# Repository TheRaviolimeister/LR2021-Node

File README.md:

# LR2021 Node

**A self-built LoRa mesh node with two Semtech LR2021 radios** (868 MHz + 433 MHz, both also 2.4 GHz).
It speaks **Meshtastic**, listens to **MeshCore** and has its own amateur-radio protocol for
text, images and files. Controlled by an app for Android, iOS, Windows and Linux – over Wi-Fi, Bluetooth,
USB or a serial cable.

## Hardware

| Part | Role |
|---|---|
| Orange Pi Zero 2W | the brain: runs the node service, Wi-Fi hotspot, Bluetooth, web UI |
| 2× ESP32-S3 DevKitC-1 | radio modems, one per LR2021 |
| Waveshare Core2021-HF / -LF (LR2021) | 850–930 MHz and 410–510 MHz, plus 2.4 GHz |
| GPS L76X | position |
| CP2102 | serial console / cable connection to the PC app |

Full part list: [docs/hardware/parts-list.md](docs/hardware/parts-list.md) ·
assembly and wiring: [docs/hardware/assembly.md](docs/hardware/assembly.md) ·
carrier PCB (ready to order): [hardware/carrier](hardware/carrier/README.md)

## Software

| Folder | Content | Docs |
|---|---|---|
| `firmware/` | ESP32 modem firmware (Arduino, RadioLib) | [docs/firmware.md](docs/firmware.md) |
| `Node/` | SD card image for the Orange Pi (Armbian), node service `lr2021d` | [docs/node.md](docs/node.md) |
| `App/source/` | Flutter app (Android, iOS, Windows, Linux) | [docs/app.md](docs/app.md) |
| `host/`, `modem_tool.py` | Python tools for testing modems on a PC | [docs/firmware.md](docs/firmware.md) |
| `docs/modem-protocol.md` | serial protocol between node and modems | – |

## Download

Ready-to-use builds are in the [releases](../../releases/latest): app for Android, iOS, Windows and Linux,
both modem firmwares and the node update package. The app updates itself from there.

## Building a node

1. Get the parts ([part list](docs/hardware/parts-list.md)) and wire them ([assembly](docs/hardware/assembly.md)).
2. Flash `LR2021-Modem-A.bin` to ESP32 A and `LR2021-Modem-B.bin` to ESP32 B ([firmware](docs/firmware.md)).
3. Build and write the SD card image ([node](docs/node.md)).
4. Install the app, connect to the node's Wi-Fi `LR2021-xxxx` and pick “Network (Pi)” ([app](docs/app.md)).

Transmitting on 70 cm with full power and the own LR protocol requires an amateur radio licence.
The app enforces the legal power limits for the license-free bands.

## Documentation

- Part list: [docs/hardware/parts-list.md](docs/hardware/parts-list.md)
- Assembly and wiring: [docs/hardware/assembly.md](docs/hardware/assembly.md)
- Carrier PCB (KiCad, Gerber, BOM): [hardware/carrier](hardware/carrier/README.md)
- ESP32 firmware: [docs/firmware.md](docs/firmware.md)
- Node software (SD card): [docs/node.md](docs/node.md)
- App: [docs/app.md](docs/app.md)
- Modem protocol: [docs/modem-protocol.md](docs/modem-protocol.md)
- Transmit power and licence: [docs/tx-power.md](docs/tx-power.md)

## License

- Software and firmware: **GPL-3.0** ([LICENSE](LICENSE))
- Hardware documentation (wiring, part list, plans): **CERN-OHL-S-2.0** ([LICENSE-HARDWARE](LICENSE-HARDWARE))
- **Attribution required:** see [NOTICE](NOTICE).

© 2026 Raviolimeister (RAV1805)

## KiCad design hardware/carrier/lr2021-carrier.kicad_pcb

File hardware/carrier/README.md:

# LR2021 Node – carrier board

A 172 × 106 mm two-layer PCB that replaces the perfboard and the point-to-point wiring. All modules
stay pluggable: the Orange Pi Zero 2W, both ESP32-S3 DevKitC-1 and both Core2021 modules sit in
female headers with generous space between them. The four antenna connectors are soldered to the
board, and the small SMD parts can be assembled by the PCB manufacturer. The 868 MHz path has a
1 W front end (power amplifier, low-noise amplifier with bypass) and a socket for a plug-in filter.

> Revision 1.3 has not been manufactured yet. Before ordering, print `fabrication/layout.svg` at
> 100 % and check the header positions against your own modules.

## Layout

```
 top edge:                 [868 LoRa]  [2.4G HF]  I2C I2C  [2.4G LF]  [433 LoRa]   I2C I2C I2C
             USB-C / J1  868 PA/LNA  Core2021-HF               Core2021-LF
             power input  filter      (both modules at the same height, mirrored)
                                    I2C  I2C  I2C  I2C  I2C
             ESP32 A            I2C header                                     ESP32 B
             (USB at the        I2C header  CONSOLE  GPS                       (USB at the
              bottom edge)  USB  Orange Pi Zero 2W (ports at the bottom edge)   bottom edge)
                         console
```

The layout is mirror-symmetric about the vertical centre line: both radio modules sit at the same
height, both ESP32 at the same distance from the side edges. The connectors for the console
adapter, GPS and I²C sit in the middle, directly above the Orange Pi pins they belong to. The USB
console (USB-C, CH340C, TX/RX LEDs) sits between ESP32 A and the Orange Pi at the bottom edge.
Signals run on the top layer; the bottom layer is a ground plane that is only interrupted by short
crossings (mainly where the I²C bus branches to the sockets). The bus between each ESP32 and its
radio module is routed without crossings: the lines of ESP32 A run in parallel along the left
edge and over the top end of its socket, the 5 V rail runs along the left edge and under the USB end
of ESP32 A and continues under the Orange Pi. The USB-C receptacle, the ESD protection and the
USB data lines have a fixed fan-out (0.5 mm pin pitch).

## Features

- **Four SMA antenna connectors (90°, through hole) on the top edge:** 868 MHz LoRa on the left,
  433 MHz LoRa on the right, the two 2.4 GHz connectors in the middle.
  - **RF lines:** each module pin is connected to its connector by a 50 Ω line (grounded
    coplanar waveguide: 1.55 mm track, 0.3 mm gap, solid ground underneath, ground via fence on
    both sides; calculated for the standard 1.6 mm FR4 two-layer stack). No other signal crosses
    or runs underneath an RF line. Lengths: 433 MHz and 2.4 GHz (LF module) about 17 mm,
    2.4 GHz (HF module) 36 mm, 868 MHz 19 mm module → filter socket, 9 mm filter socket → front end,
    10 mm front end → connector. A matched line of this length does not radiate; the loss is below
    0.05 dB (433 MHz), about 0.15 dB (868 MHz, all pieces) and about 0.3 dB (2.4 GHz, HF module).
  - **π network at every connector:** series 0 Ω resistor (fitted), a free 0603 shunt place on the
    module side (for a later low-pass or matching network, see "RF filters" below; on the 868 MHz
    line this place is the fitted 2.7 pF capacitor of the front end's antenna low-pass) and a shunt
    inductor to ground right at the connector.
  - **ESD protection:** the shunt inductor (L10 868 MHz: 68 nH, L11/L12 2.4 GHz: 15 nH, L13 433 MHz:
    100 nH, Murata LQG18HN) drains static charge from the antenna and its cable to ground. Its
    self-resonance lies just above the band (≥ 1.0 GHz, ≥ 2.8 GHz, ≥ 0.8 GHz), so in the band it is
    several hundred ohms: worst case 0.02–0.05 dB, in practice not measurable. The antenna ports of
    the radio modules and of the front end carry no DC (antennas may be DC shorts), so the DC path is
    harmless. This matters most for the front end (SE2435L: 1 kV HBM).
- **868 MHz front end (U8, Skyworks SE2435L):** see the section below – up to +30 dBm (1 W) at the
  connector, a low-noise amplifier with bypass that the firmware switches by the measured noise
  floor, and the plug-in filter socket J22.
- **Ten Qwiic / STEMMA QT sockets plus two 4-pin headers for I²C peripherals** (display, buttons,
  switches, sensors, I/O expanders). All of them are on the same bus: Orange Pi pins 3 (SDA) and
  5 (SCL), 4.7 kΩ pull-ups to 3.3 V. **3.3 V only:** do not connect modules that pull SDA/SCL up
  to 5 V.
- **One protected 5 V input:** USB-C (power only) or JST-XH J1 for the 18650 battery shield, with
  reverse-polarity protection (2 × P-MOSFET), 3 A resettable fuse, TVS diode and a power LED.
- **No back-feeding:** each ESP32 gets its 5 V through a Schottky diode, so a PC on the ESP32's USB
  port cannot feed the node's 5 V rail. All UART lines between the modules and to the console
  have 1 kΩ series resistors, so nothing is powered through the data lines when only one side
  is switched on. The console connector has no supply pin.
- **ESP32 reset and boot from the Orange Pi:** the Pi can pull EN and GPIO0 of each ESP32 low via
  a MOSFET (Pi pins 29/31 = EN/GPIO0 of ESP32 A, pins 32/33 = EN/GPIO0 of ESP32 B; high = pulled
  low). 10 kΩ pull-down resistors keep the MOSFETs off (ESP32 running) while the Pi boots or the
  Pi pins are not configured.
- **LR2021 DIO7 and DIO8** are connected to GPIO8 and GPIO9 of both ESP32 (not used by the
  current firmware, reserved).
- **USB console on the board:** USB-C J21 ("USB CONSOLE") with a CH340C USB serial converter and
  USBLC6-2SC6 ESD protection. It is the Orange Pi's debug console (UART0, 115200 Bd) and the
  "Node cable" connection of the app – one USB-C cable from the PC is enough. Two LEDs show the
  traffic: **TX** (red) = PC to node, **RX** (green) = node to PC.
  - The CH340C runs from the node's 3.3 V, the 5 V of the PC is not used at all (WCH self-powered
    mode). No current can flow between PC and node through the data lines, and the PC cannot feed
    the node. The COM port therefore only appears while the node is switched on.
  - Windows 10/11 installs the CH340 driver automatically (otherwise: WCH "CH341SER"); Linux and
    Android (USB-OTG) support it out of the box. The app recognises it as the node console.
- **Console adapter connector:** J3 (GND, RXD, TXD) for an external USB serial adapter such as the
  CP2102 module, in parallel to the on-board converter. Use only one of them at a time. Connect only
  GND, RXD and TXD of the adapter, not its 3.3 V / 5 V pin.
- Decoupling capacitors at both radio modules, an extra 22 µF at the Orange Pi's 5 V pins, GPS
  connector with PPS, ground planes on both layers.
- **Mounting holes:** M3 in the two top corners and two under the USB ends of the ESP32 sockets
  (mount the board before plugging in the ESP32). Orange Pi pin 6 (GND) is not connected on the
  carrier – it is connected to the other GND pins inside the Pi.

## 868 MHz front end

```
 Core2021-HF ── J22 filter socket ── SE2435L TR ─┬─ LNA (16 dB) / bypass ──┐
  (LORA_ANT)     (plug-in SAW)                   └─ PA (26 dB, up to 1 W) ─┴─ ANT1 ── low-pass ── SMA 868
```

- **U8 Skyworks SE2435L** (860–930 MHz front-end module): power amplifier up to +30 dBm, low-noise
  amplifier (16 dB gain, 2 dB noise figure) with bypass, transmit/receive switch. The output match
  (L2, C30, C31, L1), the harmonic traps (L7/C32 at the PA output, L9/C33 at the antenna side), the
  antenna low-pass (L8, L6, C9) and the supply decoupling follow the Skyworks SE2435L-EK5 evaluation
  board (+30 dBm, 868–930 MHz, ETSI/FCC). The values are a starting point: on a two-layer board the
  output match may need a small correction for the very last dB – check with a power meter.
- **Supply:** U9 TLV75901 (1 A LDO) makes 4.68 V for the front end from the 5 V rail, behind a
  ferrite bead (FB1). At +30 dBm the front end draws about 0.55 A while transmitting; the 5 V
  source has to deliver this on top of the rest of the node. The exposed pad of U8 has nine vias
  into the bottom ground plane as a heat sink.
- **Filter socket J22** (1×5 female header: GND, port 1, GND, port 2, GND): sits between the radio
  module and the front end. When receiving, the filter is behind the LNA, so its loss costs almost
  no sensitivity, and strong signals outside the band (e.g. LTE 800 directly below 868 MHz) never
  reach the LR2021. When transmitting, only the drive level of a few mW passes the filter, so a small
  SAW filter is enough. The filter module is described in [hardware/filter868](../filter868); for a
  different band (another radio module, 915 MHz, …) plug in a module with a matching filter.
  **Without a filter module the 868 MHz path is open:** bridge pin 2 and pin 4 of J22 with a short
  wire instead, and set the filter loss of the calibration to 0 (on the node:
  `python3 /opt/lr2021/lrmodem.py -p socket://127.0.0.1:2021 fe --filter-loss 0`). The factory
  value assumes the module (3 dB); with a bridge and 3 dB the output would be 3 dB above the target
  and above the legal limit.
- **Control from ESP32 A:** GPIO42 = CSD (front end on), GPIO41 = CPS (LNA on / bypass),
  GPIO40 = CTX (transmit via the PA), each through 1 kΩ. The three lines run in parallel next to the
  filter socket and cross the bus of ESP32 A once, with one via each, on the bottom layer. A 10 kΩ pull-down on CSD keeps the front end
  switched off while the ESP32 starts; the firmware detects the front end by this pull-down.
- **Firmware (1.1.0 or newer required):**
  - The transmit power set by the app is the power at the connector. The firmware converts it into
    the LR2021 drive level: from 14 dBm upwards the signal goes through the PA, below that through
    the bypass (up to about 3 dBm; requests between 4 and 13 dBm are sent with these 3 dBm, never more).
  - **The legal limits are enforced in the firmware**, whatever the app asks for: 27 dBm (500 mW ERP)
    in 869.40–869.65 MHz (Meshtastic EU_868, MeshCore), 14 dBm (25 mW ERP) everywhere else; both
    assume an antenna gain of up to 2.15 dBi. The hardware alone could do more (+30 dBm). At the band
    edges the firmware allows 40 kHz for the crystal correction of the app (the frequency it programs
    is offset by the measured crystal error, the transmitted one is not).
  - **LNA automatic (default):** every 5 minutes the firmware measures the noise floor with and
    without the LNA. If the receiver's own noise limits the sensitivity (quiet site), the LNA stays
    on; if the noise from outside dominates (city, a transmitter nearby), the LNA would not improve
    anything and only make the receiver easier to overload – then it switches to bypass. The mode
    (automatic / on / off) and the measured noise floor are shown in the app (Radio → Modem).
- **Never flash firmware older than 1.1.0 onto ESP32 A on this board.** Older firmware does not
  know the front end and could drive its input (max. +10 dBm) with up to +22 dBm.

## RF filters

- **868 MHz:** plug-in SAW filter (J22, see above); the front end itself has a low-pass with two
  harmonic traps at its output. An external cavity filter on the SMA connector is still possible
  (needs to be rated for 1 W).
- **433 MHz:** no filter fitted. The SMD filters that can be assembled are made for a single channel
  and are not rated for the transmit power; against strong signals next to the band use an external
  cavity filter on the SMA connector.
- **2.4 GHz:** no filter. An LTCC band-pass filter (e.g. Murata LFB182G45SG9B740, 0.7 dB, 500 mW)
  would fit, but it passes 2400–2500 MHz only and would cut off the 13 cm amateur band below
  2400 MHz.
- The free module-side shunt places of the π networks allow a low-pass filter for transmitter
  harmonics if a measurement ever shows the need (e.g. 433 MHz: 5.6 pF shunt + the 0 Ω replaced by
  27 nH; C0G capacitors, high-Q wire-wound inductors).

## Checks of the design

`check_board.py` and the design rule check cover:

- every connection against the pin names of the modules and parts (ESP32-S3-DevKitC-1, Core2021,
  Orange Pi Zero 2W header from the vendor's pin table, firmware pin numbers, CH340C, USBLC6-2SC6,
  USB-C receptacle, MOSFETs, diodes, SE2435L, TLV75901 – all taken from the data sheets), including
  the complete topology of the front end (match, traps, low-pass, supply feeds, control lines) and
  its supply voltage (4.68 V, recommended 4.0–4.8 V);
- no net with only one connection, no short, all nets connected; in addition to the design rule check
  `check_board.py` compares every piece of copper (tracks, vias, pads, planes) with every other one of a
  different net and reports anything touching or closer than 0.15 mm; minimum distance between parts
  (0.25 mm between the outlines; small passives and the front-end chips may touch outlines, which
  still leaves at least 0.5 mm between the bodies);
- RF lines: 48.5–51.9 Ω for the JLCPCB 1.6 mm stack-up (εr 4.2–4.8), ground plane continuous under
  and beside the lines (gaps only at the connector and module pins), via fence ≤ λ/40, no other
  track closer than 2.4 mm;
- supply: 5 V path to the Orange Pi 58 mΩ (≈ 0.09 V at 1.5 A), 1.6 mm wide.

## Radio modules: antenna signal on the pins

The Core2021 has an IPEX socket and, in parallel, the antenna signal on pin 1 (2.4 GHz) and
pin 16 (LoRa) – but only if the 0 Ω resistors R2 (2.4 GHz) and R3 (LoRa) next to the IPEX
sockets on the module are fitted. Check it with a multimeter: pin 16 to the centre contact of the
LoRa IPEX socket, and pin 1 to the centre contact of the 2.4 GHz socket, must read about 0 Ω. If
not, bridge R2/R3 with a 0402 0 Ω resistor or a solder bridge. Leave the IPEX sockets empty.

- R2 and R3 have no outline in the silkscreen; the two small pads sit right next to the IPEX
  sockets, beside the printed "R2"/"R3". If the IPEX sockets are not needed, removing them with hot
  air (small nozzle, low air flow, neighbouring parts covered with Kapton tape) makes the pads much
  easier to reach; the empty IPEX pads do not matter at these frequencies.
- On the **Core2021-HF**, pin 16 reads as a short to GND once R3 is bridged: a 22 nH shunt inductor
  (L11) sits on the LoRa line. That is normal. The Core2021-LF has no such inductor (and a series
  capacitor), and the 2.4 GHz lines of both modules have none, so these pins must *not* read as a
  short to GND.
- Effect measured on the perfboard prototype after bridging: about +52 dB on the 2.4 GHz link
  between the two modules, about +39 dB at 433 MHz and about +25 dB at 868 MHz.

## Ordering (e.g. JLCPCB)

1. Upload `fabrication/lr2021-carrier-gerber.zip`. Settings: 2 layers, **1.6 mm**, 1 oz copper,
   FR4, any colour, HASL or ENIG. (The RF line width is calculated for this stack-up.)
2. For assembly: enable "PCB Assembly", top side, upload `fabrication/bom.csv` and
   `fabrication/cpl.csv`. The SMA connectors are through-hole parts – choose the option that
   includes through-hole assembly, or solder them yourself. Check the parts preview: diodes
   (D1–D4), transistors (Q1–Q6), the front end U8 and its LDO U9 (pin 1 mark), U6/U7, the Qwiic
   sockets and the SMA connectors must match the marks on the board; correct the rotation there if
   needed.
3. The remaining through-hole parts are soldered by hand, see `fabrication/hand-solder.csv`.

Other assembly services (NextPCB, PCBWay, …) need manufacturer part numbers and often Excel files:
use `fabrication/bom-mpn.xlsx` (or `.csv`: designators, quantity per board, manufacturer part
number, manufacturer, LCSC number) as BOM and `fabrication/cpl.xlsx` as centroid / pick-and-place
file. `make_assembly_files.py` creates them from `bom.csv` and `cpl.csv` (also for `filter868`).

## Assembly

| Position | Part | Note |
|---|---|---|
| U1 / U2 | 2 × female header 1×22 each | ESP32 A / B, USB connectors at the bottom edge. The inner row has two positions: **22.86 mm** (original Espressif DevKitC-1) and **25.4 mm** (many N16R8 boards). Measure the distance between the pin rows of your board and solder the header into the matching row. |
| U3 | 2 × female header 1×8 | Core2021-**HF** (868 MHz), IPEX sockets pointing down |
| U4 | 2 × female header 1×8 | Core2021-**LF** (433 MHz), IPEX sockets pointing up |
| U5 | female header 2×20 | Orange Pi Zero 2W: solder the 2×20 male header to the **underside** of the Pi, then plug it in component side up; the ports face the bottom edge |
| J13–J16 | SMA jack 90°, through hole | antennas: J13 868 MHz, J14 2.4 GHz (HF), J15 2.4 GHz (LF), J16 433 MHz |
| J1 | JST-XH 2-pin | 5 V input from the battery shield (+ on the left) |
| J2 | JST-XH 5-pin | GPS: 3V3, GND, TX, RX, PPS – labels = pins of the GPS module (GPS TX to “TX”) |
| J3 | pin header 1×3 | console adapter (optional, e.g. CP2102): GND, RXD, TXD – labels = pins of the adapter (adapter RXD to “RXD”); no supply pin |
| J21 | USB-C (assembled) | USB console, see above |
| J22 | female header 1×5 | 868 MHz filter module ([hardware/filter868](../filter868)); without a module bridge pin 2 and pin 4 |
| J4, J12 | pin header 1×4 | I²C: GND, VCC (3.3 V), SCL, SDA |
| J6–J11, J17–J20 | JST SH 4-pin (Qwiic) | I²C: GND, 3.3 V, SDA, SCL (assembled) |

**Only one 5 V source at a time:** USB-C on the board, J1, or the Pi's own USB-C. Never transmit
without an antenna on the connector of the active band.

## Signals

| Signal | Orange Pi pin | ESP32 / module |
|---|---|---|
| UART4 TX / RX (500000 Bd) | 7 / 16 | ESP32 A GPIO1 / GPIO2 |
| UART3 TX / RX (500000 Bd) | 28 / 27 | ESP32 B GPIO1 / GPIO2 |
| UART5 TX / RX (9600 Bd) | 11 / 13 | GPS RX / TX, PPS on pin 15 |
| UART0 TX / RX (console) | 8 / 10 | CH340C (J21) and J3 |
| I²C SDA / SCL | 3 / 5 | J4, J12, all Qwiic sockets |
| EN / GPIO0 ESP32 A | 29 / 31 | via MOSFET, high = low on the ESP32 |
| EN / GPIO0 ESP32 B | 32 / 33 | via MOSFET, high = low on the ESP32 |

On the carrier board ESP32 A is on UART4 and ESP32 B on UART3 (the perfboard prototype uses the
opposite assignment). This keeps every connection on its own side of the board. The node software
identifies the two modems by their role (GET_INFO), so nothing has to be configured.

ESP32 ↔ LR2021 as in [assembly.md](../../docs/hardware/assembly.md), plus DIO7 → GPIO8 and
DIO8 → GPIO9. ESP32 A also controls the 868 MHz front end: GPIO42 = CSD, GPIO41 = CPS,
GPIO40 = CTX.

## Files

| File | Content |
|---|---|
| `generate_board.py` | generates the complete board (footprints, placement, nets, RF lines, routing, ground planes) |
| `astar.c` | path search used by the router (compiled automatically with gcc) |
| `make_outputs.py` | design rule check, Gerber/drill, BOM, placement, renders |
| `check_board.py` | checks every connection against the pin names of the modules, track lengths and part spacing |
| `lr2021-carrier.kicad_pcb` | the KiCad 9 board – can be opened and edited in KiCad |
| `netlist.json` | all connections |
| `fabrication/` | files for ordering and pictures |
| `../filter868/` | the plug-in 868 MHz filter module (own small board) |

Rebuild (Linux or WSL with KiCad 9, `python3-numpy`, `python3-scipy`, `gcc`):

```
python3 generate_board.py
python3 make_outputs.py
python3 check_board.py
```

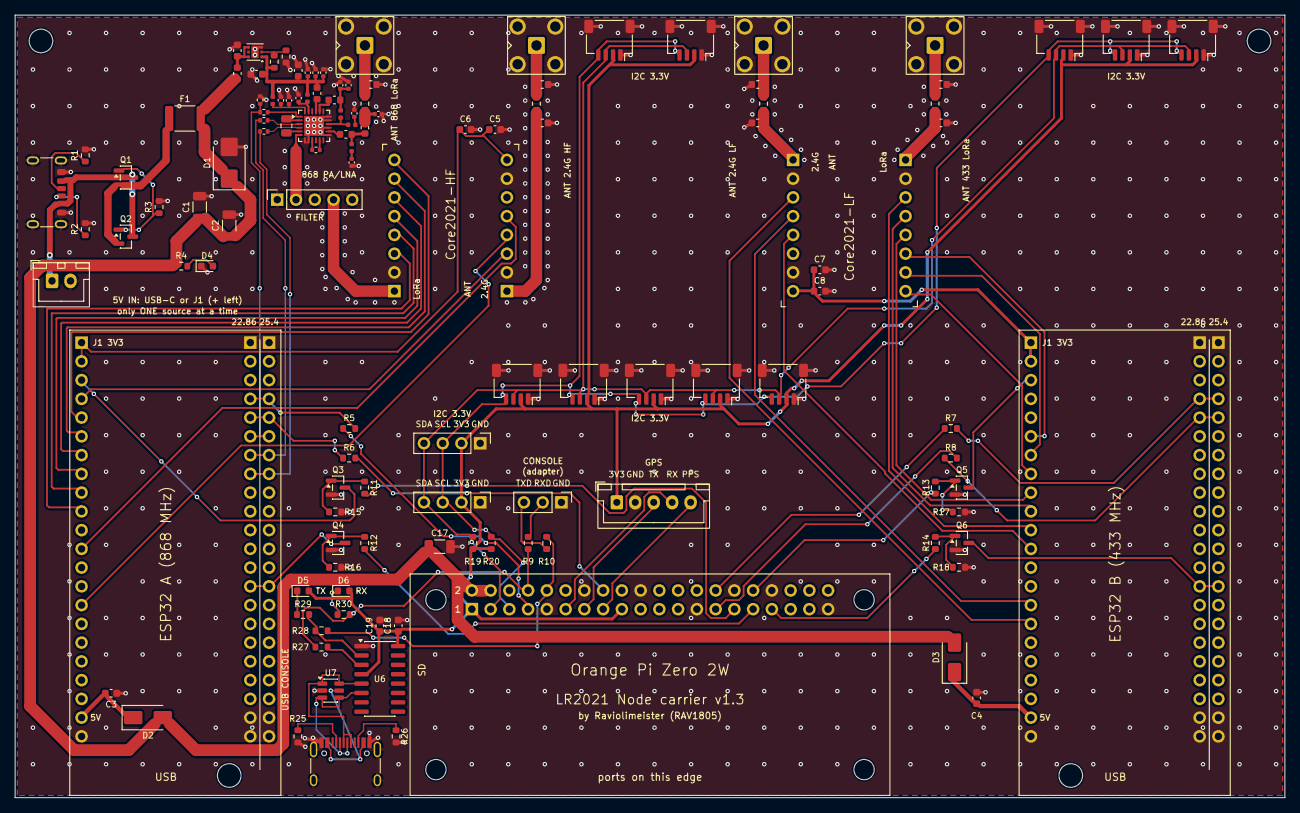
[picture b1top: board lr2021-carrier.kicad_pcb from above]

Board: 2 copper layers, 172.0 x 106.0 mm, 128 parts (0 on the bottom side), 102 nets.

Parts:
C1, C2, C17: 22uF; C_1206_3216Metric
C3, C4, C5, C7, C20, C21: 10uF; C_0603_1608Metric
C6, C8, C18: 100nF; C_0603_1608Metric
C9: 2.7pF; C_0402_1005Metric
C11, C13, C15: DNP; C_0603_1608Metric
C19, C22: 4.7uF; C_0603_1608Metric
C23: 10nF; C_0402_1005Metric
C24: 1nF; C_0402_1005Metric
C25, C27: 100pF; C_0402_1005Metric
C26: 22pF; C_0402_1005Metric
C28: 47pF; C_0402_1005Metric
C30: 10pF; C_0402_1005Metric
C31: 5pF; C_0402_1005Metric
C32: 3.9pF; C_0402_1005Metric
C33: 3.3pF; C_0402_1005Metric
C35: 3.3pF; C_0805_2012Metric
D1: SMBJ5.0A; D_SMB
D2, D3: SS34; D_SMA
D4, D5: LED red; LED_0603_1608Metric
D6: LED green; LED_0603_1608Metric
F1: PTC 3A; Fuse_1812_4532Metric
FB1: BLM18PG221; L_0603_1608Metric
H1, H2, H3, H4: M3; MountingHole_3.2mm_M3
J1: 5V IN; JST_XH_B2B-XH-A_1x02_P2.50mm_Vertical
J2: GPS; JST_XH_B5B-XH-A_1x05_P2.50mm_Vertical
J3: CONSOLE; PinHeader_1x03_P2.54mm_Vertical
J4, J12: I2C; PinHeader_1x04_P2.54mm_Vertical
J5: USB-C power; USB_C_Receptacle_GCT_USB4125-xx-x_6P_TopMnt_Horizontal
J6, J7, J8, J9, J10, J11, J17, J18, J19, J20: Qwiic; JST_SH_SM04B-SRSS-TB_1x04-1MP_P1.00mm_Horizontal
J13: SMA 868 LoRa; SMA_BAT_Wireless_BWSMA-KWE-Z001
J14: SMA 2.4G HF; SMA_BAT_Wireless_BWSMA-KWE-Z001
J15: SMA 2.4G LF; SMA_BAT_Wireless_BWSMA-KWE-Z001
J16: SMA 433 LoRa; SMA_BAT_Wireless_BWSMA-KWE-Z001
J21: USB-C console; USB_C_Receptacle_HRO_TYPE-C-31-M-12
J22: 868 filter; PinSocket_1x05_P2.54mm_Vertical
L1: 6.8nH; L_0402_1005Metric
L2: 1.2nH; L_0603_1608Metric
L3, L4: 39nH; L_0402_1005Metric
L5: 6.8nH; L_0603_1608Metric
L6: 8.2nH; L_0603_1608Metric
L7: 1.0nH; L_0402_1005Metric
L8: 5.6nH; L_0603_1608Metric
L9: 1.5nH; L_0402_1005Metric
L10: 68nH; L_0603_1608Metric
L11, L12: 15nH; L_0603_1608Metric
L13: 100nH; L_0603_1608Metric
Q1, Q2: AO3401A; SOT-23
Q3, Q4, Q5, Q6: 2N7002; SOT-23
R1, R2, R25, R26: 5.1k; R_0603_1608Metric
R3, R15, R16, R17, R18, R32: 10k; R_0603_1608Metric
R4, R5, R6, R7, R8, R9, R10, R11, R12, R13, R14, R27, R29, R30: 1k; R_0603_1608Metric
R19, R20, R28: 4.7k; R_0603_1608Metric
R21, R22, R23, R24: 0R; R_0603_1608Metric
R31: 75k; R_0603_1608Metric
R33: 0R; R_0402_1005Metric
R34, R35, R36: 1k; R_0402_1005Metric
R37: 10k; R_0402_1005Metric
U1, U2: ESP32-S3-DevKitC-1; ESP32-S3-DevKitC-1_Socket
U3: Core2021-HF; Core2021_Socket
U4: Core2021-LF; Core2021_Socket
U5: Orange Pi Zero 2W; OrangePi_Zero2W_Socket
U6: CH340C; SOIC-16_3.9x9.9mm_P1.27mm
U7: USBLC6-2SC6; SOT-23-6
U8: SE2435L-R; QFN-24-1EP_4x4mm_P0.5mm_EP2.7x2.7mm
U9: TLV75901; WSON-6-1EP_2x2mm_P0.65mm_EP1x1.6mm

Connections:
+3V3_A: C5.1, C6.1, U1.1, U1.2, U3.8
+3V3_B: C7.1, C8.1, U2.1, U2.2, U4.8
+3V3_PI: C18.1, C19.1, D5.2, D6.2, J2.1, J4.2, J6.2, J7.2, J8.2, J9.2, J10.2, J11.2, J12.2, J17.2, J18.2, J19.2, J20.2, R19.1, R20.1, U5.1, U5.17, U6.4, U6.16
+5V: C1.1, C2.1, C17.1, D1.1, D2.2, D3.2, F1.2, FB1.1, R4.1, U5.2, U5.4
+5V_ESPA: C3.1, D2.1, U1.21
+5V_ESPB: C4.1, D3.1, U2.21
A_RXD: R5.2, U1.26
A_TXD: R6.1, U1.27
BUSY_A: U1.5, U3.16
BUSY_B: U2.8, U4.16
B_RXD: R7.2, U2.26
B_TXD: R8.1, U2.27
CC1: J5.A5, R1.1
CC1_U: J21.A5, R25.2
CC2: J5.B5, R2.1
CC2_U: J21.B5, R26.2
CON_RXD: J3.3, R10.1
CON_TXD: J3.2, R9.2
CPS_A: R35.1, U1.29
CSD_A: R34.1, R37.1, U1.28
CS_A: U1.10, U3.11
CS_B: U2.11, U4.11
CTX_A: R36.1, U1.30
C_RXD: R27.2, U6.3
C_TXD: R28.1, R29.2, U6.2
DIO7_A: U1.12, U3.5
DIO7_B: U2.12, U4.5
DIO8_A: U1.15, U3.4
DIO8_B: U2.15, U4.4
EN_A: Q3.3, U1.3
EN_B: Q5.3, U2.3
FE_ANT1: L8.1, U8.14
FE_CPS: R35.2, U8.3
FE_CSD: R34.2, U8.1
FE_CTX: R36.2, U8.4
FE_LNAIN: R33.1, U8.9
FE_N1: C30.1, C31.1, L1.2, L2.2
FE_N3: L6.1, L8.2, L9.2
FE_PAIN: C35.2, U8.2
FE_PAOUT: L2.1, U8.20
FE_RXFLT: R33.2, U8.11
FE_TRAP1: C32.1, L7.2
FE_TRAP2: C33.2, L9.1
FE_TXFLT: C35.1, U8.5
FE_TXIN: L1.1, L7.1, U8.16
FE_VCC0: C26.1, L3.1, U8.23
FE_VCC1: C27.1, C28.1, L4.1, U8.24
FE_VCC2: L5.1, U8.21
GND: C1.2, C2.2, C3.2, C4.2, C5.2, C6.2, C7.2, C8.2, C9.2, C11.2, C13.2, C15.2, C17.2, C18.2, C19.2, C20.2, C21.1, C22.2, C23.2, C24.2, C25.2, C26.2, C27.2, C28.2, C30.2, C31.2, C32.2, C33.1, D1.2, D4.1, J1.2, J2.2, J3.1, J4.1, J5.A12, J5.B12, J5.S1, J6.1, J6.MP, J7.1, J7.MP, J8.1, J8.MP, J9.1, J9.MP, J10.1, J10.MP, J11.1, J11.MP, J12.1, J13.2, J14.2, J15.2, J16.2, J17.1, J17.MP, J18.1, J18.MP, J19.1, J19.MP, J20.1, J20.MP, J21.A1, J21.A12, J21.B1, J21.B12, J21.S1, J22.1, J22.3, J22.5, L10.2, L11.2, L12.2, L13.2, Q3.2, Q4.2, Q5.2, Q6.2, R1.2, R2.2, R3.2, R15.2, R16.2, R17.2, R18.2, R25.1, R26.1, R32.2, R37.2, U1.22, U1.23, U1.43, U1.44, U2.22, U2.23, U2.43, U2.44, U3.2, U3.7, U3.10, U4.2, U4.7, U4.10, U5.9, U5.14, U5.20, U5.25, U5.30, U5.34, U5.39, U6.1, U7.2, U8.7, U8.8, U8.13, U8.15, U8.17, U8.18, U8.25, U9.3, U9.7
GPS_PPS: J2.5, U5.15
GPS_RX: J2.4, U5.11
GPS_TX: J2.3, U5.13
G_ENA: Q3.1, R11.2, R15.1
G_ENB: Q5.1, R13.2, R17.1
G_IO0A: Q4.1, R12.2, R16.1
G_IO0B: Q6.1, R14.2, R18.1
I2C_SCL: J4.3, J6.4, J7.4, J8.4, J9.4, J10.4, J11.4, J12.3, J17.4, J18.4, J19.4, J20.4, R20.2, U5.5
I2C_SDA: J4.4, J6.3, J7.3, J8.3, J9.3, J10.3, J11.3, J12.4, J17.3, J18.3, J19.3, J20.3, R19.2, U5.3
IO0_A: Q4.3, U1.36
IO0_B: Q6.3, U2.36
IRQ_A: U1.4, U3.3
IRQ_B: U2.16, U4.3
LED_A: D4.2, R4.2
LED_RX: D6.1, R30.1
LED_TX: D5.1, R29.1
MISO_A: U1.7, U3.14
MISO_B: U2.6, U4.14
MOSI_A: U1.8, U3.13
MOSI_B: U2.9, U4.13
NRST_A: U1.6, U3.15
NRST_B: U2.7, U4.15
PA_FB: R31.2, R32.1, U9.2
PA_VCC: C21.2, C22.1, C23.1, C24.1, C25.1, L3.2, L4.2, L5.2, R31.1, U9.1
PA_VIN: C20.1, FB1.2, U9.4, U9.6
PFET_G: Q1.1, Q2.1, R3.1
PI_ENA: R11.1, U5.29
PI_ENB: R13.1, U5.32
PI_IO0A: R12.1, U5.31
PI_IO0B: R14.1, U5.33
PI_RX0: R10.2, R28.2, U5.10
PI_RX3: R8.2, U5.27
PI_RX4: R6.2, U5.16
PI_TX0: R9.1, R27.1, R30.2, U5.8
PI_TX3: R7.1, U5.28
PI_TX4: R5.1, U5.7
RF_HF_24_M: C11.1, R22.1, U3.1
RF_HF_24_S: J14.1, L11.1, R22.2
RF_HF_LORA_M: C9.1, L6.2, R21.1
RF_HF_LORA_R: J22.4, U3.9
RF_HF_LORA_S: J13.1, L10.1, R21.2
RF_HF_LORA_T: J22.2, U8.6
RF_LF_24_M: C13.1, R23.1, U4.1
RF_LF_24_S: J15.1, L12.1, R23.2
RF_LF_LORA_M: C15.1, R24.1, U4.9
RF_LF_LORA_S: J16.1, L13.1, R24.2
SCK_A: U1.9, U3.12
SCK_B: U2.10, U4.12
USB_DM: J21.A7, J21.B7, U6.6, U7.3, U7.4
USB_DP: J21.A6, J21.B6, U6.5, U7.1, U7.6
VBUS_U: J21.A4, J21.A9, J21.B4, J21.B9, U7.5
VIN: J1.1, J5.A9, J5.B9, Q1.3, Q2.3
VIN_P: F1.1, Q1.2, Q2.2

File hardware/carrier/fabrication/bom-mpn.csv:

S/N,Designator,Quantity,Manufacturer Part Number,Manufacturer,Description,Footprint,LCSC Part #,Procurement Type,Customer Note
1,"C1,C2,C17",3,CL31A226KAHNNNE,Samsung Electro-Mechanics,22uF,C_1206_3216Metric,C12891,,
2,"C3,C4,C5,C7,C20,C21",6,CL10A106KP8NNNC,Samsung Electro-Mechanics,10uF,C_0603_1608Metric,C19702,,
3,"C6,C8,C18",3,CC0603KRX7R9BB104,YAGEO,100nF,C_0603_1608Metric,C14663,,
4,C9,1,GJM1555C1H2R7BB01D,Murata,2.7pF,C_0402_1005Metric,C76904,,
5,"C19,C22",2,CL10A475KO8NNNC,Samsung Electro-Mechanics,4.7uF,C_0603_1608Metric,C19666,,
6,C23,1,CL05B103KB5NNNC,Samsung Electro-Mechanics,10nF,C_0402_1005Metric,C15195,,
7,C24,1,0402B102K500NT,FH,1nF,C_0402_1005Metric,C1523,,
8,"C25,C27",2,0402CG101J500NT,FH,100pF,C_0402_1005Metric,C1546,,
9,C26,1,0402CG220J500NT,FH,22pF,C_0402_1005Metric,C1555,,
10,C28,1,0402CG470J500NT,FH,47pF,C_0402_1005Metric,C1567,,
11,C30,1,GJM1555C1H100JB01D,Murata,10pF,C_0402_1005Metric,C85874,,
12,C31,1,0402CG5R0C500NT,FH,5pF,C_0402_1005Metric,C1573,,
13,C32,1,GJM1555C1H3R9BB01D,Murata,3.9pF,C_0402_1005Metric,C76907,,
14,C33,1,GJM1555C1H3R3BB01D,Murata,3.3pF,C_0402_1005Metric,C76906,,
15,C35,1,0805CG3R3C500NT,FH,3.3pF,C_0805_2012Metric,C1811,,
16,D1,1,SMBJ5.0A,Littelfuse,SMBJ5.0A,D_SMB,C83333,,
17,"D2,D3",2,SS34,MDD (Microdiode Semiconductor),SS34,D_SMA,C8678,,
18,"D4,D5",2,KT-0603R,Hubei KENTO Elec,LED red,LED_0603_1608Metric,C2286,,
19,D6,1,19-217/GHC-YR1S2/3T,Everlight,LED green,LED_0603_1608Metric,C72043,,
20,F1,1,SMD1812P300TF,RUILON,PTC 3A,Fuse_1812_4532Metric,C21004,,
21,FB1,1,BLM18PG221SN1D,Murata,BLM18PG221,L_0603_1608Metric,C80165,,
22,J5,1,USB4125-GF-A,Global Connector Technology,USB4125-GF-A,USB_C_Receptacle_GCT_USB4125-xx-x_6P_TopMnt_Horizontal,C3151650,,
23,"J6,J7,J8,J9,J10,J11,J17,J18,J19,J20",10,SM04B-SRSS-TB(LF)(SN),JST,SM04B-SRSS-TB,JST_SH_SM04B-SRSS-TB_1x04-1MP_P1.00mm_Horizontal,C160404,,
24,"J13,J14,J15,J16",4,BWSMA-KWE-Z001,BAT WIRELESS,BWSMA-KWE-Z001,SMA_BAT_Wireless_BWSMA-KWE-Z001,C496551,,through-hole part
25,J21,1,TYPE-C-31-M-12,Korean Hroparts Elec,TYPE-C-31-M-12,USB_C_Receptacle_HRO_TYPE-C-31-M-12,C165948,,
26,L1,1,LQG15HN6N8J02D,Murata,6.8nH,L_0402_1005Metric,C84403,,
27,L2,1,LQG18HN1N2S00D,Murata,1.2nH,L_0603_1608Metric,C882496,,
28,"L3,L4",2,LQG15HN39NJ02D,Murata,39nH,L_0402_1005Metric,C113055,,
29,L5,1,LQG18HN6N8J00D,Murata,6.8nH,L_0603_1608Metric,C882493,,
30,L6,1,LQG18HN8N2J00D,Murata,8.2nH,L_0603_1608Metric,C98009,,
31,L7,1,LQG15HN1N0S02D,Murata,1.0nH,L_0402_1005Metric,C97981,,
32,L8,1,LQG18HN5N6S00D,Murata,5.6nH,L_0603_1608Metric,C441735,,
33,L9,1,LQG15HN1N5S02D,Murata,1.5nH,L_0402_1005Metric,C113053,,
34,L10,1,LQG18HN68NJ00D,Murata,68nH,L_0603_1608Metric,C162555,,
35,"L11,L12",2,LQG18HN15NJ00D,Murata,15nH,L_0603_1608Metric,C98006,,
36,L13,1,LQG18HNR10J00D,Murata,100nH,L_0603_1608Metric,C98010,,
37,"Q1,Q2",2,AO3401A,AOS,AO3401A,SOT-23,C15127,,
38,"Q3,Q4,Q5,Q6",4,2N7002,JSCJ,2N7002,SOT-23,C8545,,
39,"R1,R2,R25,R26",4,0603WAF5101T5E,UNI-ROYAL,5.1k,R_0603_1608Metric,C23186,,
40,"R3,R15,R16,R17,R18,R32",6,0603WAF1002T5E,UNI-ROYAL,10k,R_0603_1608Metric,C25804,,
41,"R4,R5,R6,R7,R8,R9,R10,R11,R12,R13,R14,R27,R29,R30",14,0603WAF1001T5E,UNI-ROYAL,1k,R_0603_1608Metric,C21190,,
42,"R19,R20,R28",3,0603WAF4701T5E,UNI-ROYAL,4.7k,R_0603_1608Metric,C23162,,
43,"R21,R22,R23,R24",4,0603WAF0000T5E,UNI-ROYAL,0R,R_0603_1608Metric,C21189,,
44,R31,1,0603WAF7502T5E,UNI-ROYAL,75k,R_0603_1608Metric,C23242,,
45,R33,1,0402WGF0000TCE,UNI-ROYAL,0R,R_0402_1005Metric,C17168,,
46,"R34,R35,R36",3,0402WGF1001TCE,UNI-ROYAL,1k,R_0402_1005Metric,C11702,,
47,R37,1,0402WGF1002TCE,UNI-ROYAL,10k,R_0402_1005Metric,C25744,,
48,U6,1,CH340C,WCH,CH340C,SOIC-16_3.9x9.9mm_P1.27mm,C84681,,
49,U7,1,USBLC6-2SC6,STMicroelectronics,USBLC6-2SC6,SOT-23-6,C7519,,
50,U8,1,SE2435L-R,Skyworks,SE2435L-R,QFN-24-1EP_4x4mm_P0.5mm_EP2.7x2.7mm,C4748685,,
51,U9,1,TLV75901PDRVR,Texas Instruments,TLV75901,WSON-6-1EP_2x2mm_P0.65mm_EP1x1.6mm,C544759,,

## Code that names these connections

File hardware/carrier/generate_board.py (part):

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# the pins / lowest above the socket, the CS line is outermost and therefore the first one to turn
# into the radio module, which has CS as its lowest pin. 3V3 goes the other way (with EN/IRQ/DIO).
A_LANES = ["BUSY_A", "NRST_A", "MISO_A", "MOSI_A", "SCK_A", "CS_A"]
A_PIN = {"BUSY_A": 5, "NRST_A": 6, "MISO_A": 7, "MOSI_A": 8, "SCK_A": 9, "CS_A": 10}
LANE_PITCH = 0.65
for _k, _n in enumerate(A_LANES):
    xk = X_DKA - 1.45 - LANE_PITCH * _k
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_LF_EAST = (CX_LF + 8.7, CY_LF - 11.0, X_DKB - 1.2, CY_LF + 9.8)      # outside the LoRa pin row
B_ORDER = ["MOSI_B", "SCK_B", "CS_B", "BUSY_B", "NRST_B", "MISO_B", "DIO7_B", "DIO8_B", "IRQ_B"]   # innermost first
_B_FRONT = (CX_LF + 10.0, Y_DK - 0.5, X_DKB - 1.2, Y_DK + 19.2)       # in front of ESP32 B pins 1-8
for _n in ("MISO_B", "NRST_B", "BUSY_B"):          # vertical next to ESP32 B, then straight into the pin
    KEEPOUT[_n] = [_LF_IN, (CX_LF + 5.0, CY_LF + 9.4, CX_LF + 11.0, Y_DK + 6.0)]
for _n in ("MOSI_B", "SCK_B", "CS_B"):
    KEEPOUT[_n] = [_LF_EAST, _B_FRONT]
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
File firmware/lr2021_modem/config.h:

// LR2021 Modem-Firmware – Konfiguration
// Eine Firmware für beide ESP32. Die Rolle wird beim Kompilieren gewählt:
//   MODEM_ROLE_A  -> ESP32 A, LR2021 HF (Core2021-HF, 850–930 MHz + 2,4 GHz)
//   MODEM_ROLE_B  -> ESP32 B, LR2021 LF (Core2021-LF, 410–510 MHz + 2,4 GHz)
#pragma once
#include <stdint.h>

#define FW_VERSION_MAJOR 1
#define FW_VERSION_MINOR 2
#define FW_VERSION_PATCH 2

#if !defined(MODEM_ROLE_A) && !defined(MODEM_ROLE_B)
  #define MODEM_ROLE_A
#endif

// ---------------------------------------------------------------------------
// Pinbelegung laut Verdrahtungsplan (Schritt 3 / Schritt 4)
// ---------------------------------------------------------------------------
#if defined(MODEM_ROLE_A)
  #define MODEM_ROLE_CHAR   'A'
  #define MODEM_BAND_ID     1           // 1 = HF-Modul (868)
  #define PIN_LR_CS         17
  #define PIN_LR_IRQ        4           // LR2021 DIO11
  #define PIN_LR_RST        6
  #define PIN_LR_BUSY       5
  #define PIN_LR_MISO       7
  #define PIN_LR_MOSI       15
  #define PIN_LR_SCK        16
  // erlaubter Sub-GHz-Bereich des Moduls (Hz)
  #define SUBGHZ_MIN_HZ     850000000UL
  #define SUBGHZ_MAX_HZ     930000000UL
  // Startkonfiguration: Meshtastic EU_868 LongFast (nur Empfangsbereit, sendet nicht von selbst)
  #define DEF_FREQ_HZ       869525000UL
  #define DEF_BW_HZ         250000UL
  #define DEF_SF            11
  #define DEF_CR            5
  #define DEF_SYNC          0x2B
  #define DEF_POWER_DBM     14
  #define DEF_PREAMBLE      16
  // 868-MHz-Frontend SE2435L (PA bis 1 W, LNA mit Bypass) auf der Trägerplatine ab v1.3.
  // Wird beim Start erkannt: CSD hat dort 10k nach GND, mit internem Pull-up liest der Pin LOW.
  #define PIN_FE_CSD        42          // Frontend an (LOW = Schlaf)
  #define PIN_FE_CPS        41          // HIGH = LNA an, LOW = Bypass
  #define PIN_FE_CTX        40          // HIGH = Senden über den PA
#else
  #define MODEM_ROLE_CHAR   'B'
  #define MODEM_BAND_ID     2           // 2 = LF-Modul (433)
  #define PIN_LR_CS         18
  #define PIN_LR_IRQ        10          // LR2021 DIO11
  #define PIN_LR_RST        7
  #define PIN_LR_BUSY       15
  #define PIN_LR_MISO       6
  #define PIN_LR_MOSI       16
  #define PIN_LR_SCK        17
  #define SUBGHZ_MIN_HZ     410000000UL
  #define SUBGHZ_MAX_HZ     510000000UL
  // Startkonfiguration: 433,875 MHz, 125 kHz, SF9 (frei änderbar)
  #define DEF_FREQ_HZ       433875000UL
  #define DEF_BW_HZ         125000UL
  #define DEF_SF            9
  #define DEF_CR            5
  #define DEF_SYNC          0x12
  #define DEF_POWER_DBM     10
  #define DEF_PREAMBLE      8
  #define PIN_FE_CSD        -1          // kein Frontend am 433-MHz-Modul
  #define PIN_FE_CPS        -1
  #define PIN_FE_CTX        -1
#endif

// Frontend-Kennwerte (SE2435L-Datenblatt 860–870 MHz, VCC 4,7 V) und Steckfilter (SAW 868–870 MHz).
// Die Leistung in SET_LORA/SET_FSK gilt mit Frontend an der Antennenbuchse; die Firmware rechnet sie
// auf den LR2021-Pegel um. Richtwerte – bei Bedarf mit einem Messgerät nachstellen.
#define FE_PA_GAIN_DB       26          // Kleinsignal-Verstärkung des PA
#define FE_LNA_GAIN_DB      16
#define FE_BYPASS_LOSS_DB   2
#define FE_FILTER_LOSS_DB   3           // Steckfilter zwischen Modul und Frontend
#define FE_OUT_MAX_DBM      30          // Hardware-Maximum an der Antennenbuchse
#define FE_DRIVE_MAX_DBM    8           // LR2021-Pegel höchstens (TR-Eingang des SE2435L: max. +10 dBm)
#define FE_LEGAL_CAP        1           // EU-SRD-Grenzen immer einhalten (ERP, Antenne bis 2,15 dBi)
#define FE_FREQ_TOL_HZ      40000UL     // Toleranz an den Bandgrenzen für die Quarzkorrektur der App
#define FE_AUTO_PERIOD_MS   300000UL    // LNA-Automatik: alle 5 Minuten Rauschboden mit/ohne LNA messen
// Kalibrierung: Die vier Kennwerte oben sind nur die Startwerte. Gemessene Werte (0,1 dB genau) werden per
// FE_SET übertragen und im Flash gespeichert. Erlaubte Bereiche in 0,1 dB (Plausibilität, Tippfehler abfangen).
// Der LR2021-Pegel bleibt in jedem Fall <= FE_DRIVE_MAX_DBM, die gesetzliche Grenze wird immer angewendet.
#define FE_CAL_PA_MIN10     150
#define FE_CAL_PA_MAX10     320
#define FE_CAL_LNA_MIN10    50
#define FE_CAL_LNA_MAX10    220
#define FE_CAL_BYP_MIN10    0
#define FE_CAL_BYP_MAX10    60
#define FE_CAL_FILT_MIN10   0
#define FE_CAL_FILT_MAX10   80

// Firmware-Update über die Modem-Verbindung (OTA in den freien App-Slot der Partitionstabelle)
#define OTA_CHUNK_MAX       256         // Nutzdaten je OTA_DATA
#define OTA_IDLE_TIMEOUT_MS 30000UL     // keine OTA-Daten so lange -> Update abbrechen, Funk wieder an
#define OTA_MIN_MAJOR       1           // ältere Firmware (ohne OTA/Frontend-Steuerung) wird nicht angenommen
#define OTA_MIN_MINOR       2
#define OTA_CONFIRM_MS      120000UL    // neue Firmware: bis dahin muss ein gültiger Rahmen kommen, sonst zurück

// 2,4-GHz-Bereich (beide Module)
#define HF24_MIN_HZ         2400000000UL
#define HF24_MAX_HZ         2500000000UL

// ---------------------------------------------------------------------------
// Verbindung zum Orange Pi (UART1) und USB-Konsole (UART0)
// ---------------------------------------------------------------------------
#define PIN_HOST_RX         1           // ESP32 RX  <- Pi TX
#define PIN_HOST_TX         2           // ESP32 TX  -> Pi RX
// 500000 statt 460800: Der UART des Orange Pi Zero 2W (H618) hat 24 MHz und nur ganzzahlige Teiler
// (24 MHz / 16 / n) – 460800 würde dort zu 500000 (+8,5 %) und nichts käme an.
// 500000 ist auf beiden Seiten exakt (ESP32-S3: 80 MHz / 160, H618: 24 MHz / 16 / 3).
#define HOST_BAUD           500000
#define USB_BAUD            115200

// SPI-Takt zum LR2021. 4 MHz ist auf Lochraster mit Lackdraht sicher.
#define LR_SPI_HZ           4000000

// Status-LED (WS2812 auf dem DevKitC-1, je nach Board-Version GPIO48 oder GPIO38)
#define PIN_RGB_LED         48
#define LED_BRIGHTNESS      12

// Sicherheit: Grenzwerte, die ab Werk gelten (per Befehl änderbar, im Flash speicherbar)
#define DEF_ALLOW_SUBGHZ_TX 1
#define DEF_ALLOW_24_TX     0           // 2,4 GHz Senden aus, bis Antennen dran sind
#define DEF_MAX_PWR_SUBGHZ  22
#define DEF_MAX_PWR_24      12
#define DEF_DUTY_PERMILLE   0           // 0 = keine Begrenzung, 10 = 1 % pro Stunde

#define TX_QUEUE_LEN        8
#define CAD_TIMEOUT_MS      500
#define TX_TIMEOUT_MARGIN   1.5f        // TX-Watchdog: Faktor auf die berechnete Sendezeit
